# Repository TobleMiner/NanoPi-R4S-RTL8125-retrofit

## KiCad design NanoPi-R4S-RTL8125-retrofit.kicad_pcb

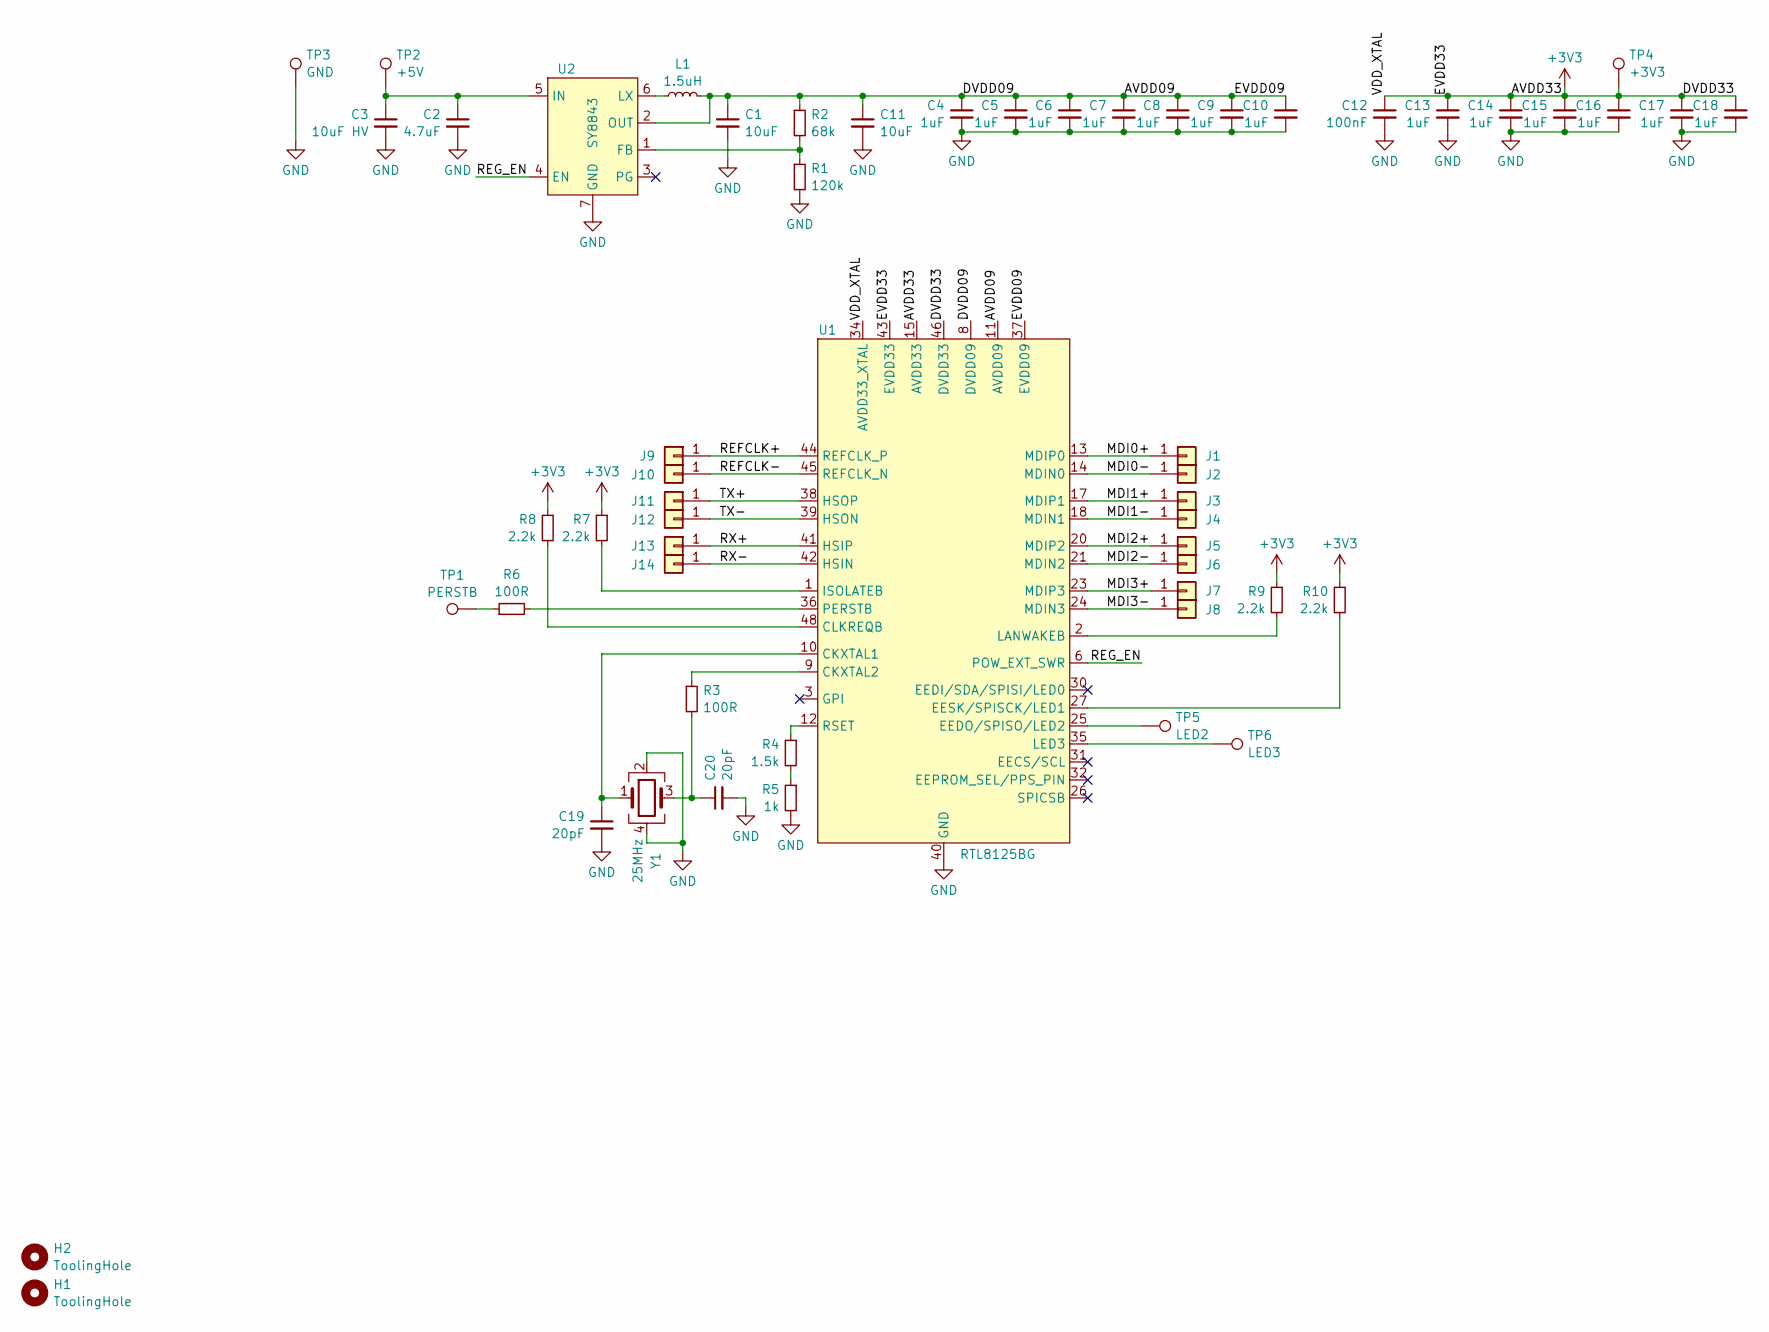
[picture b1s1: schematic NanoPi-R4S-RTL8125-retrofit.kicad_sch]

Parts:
C1, C11: 10uF; C_0402_1005Metric; LCSC C15525
C2: 4.7uF; C_0402_1005Metric; LCSC C23733
C3: 10uF HV; C_0603_1608Metric; LCSC C19702
C4, C5, C6, C7, C8, C9, C10, C13, C14, C15, C16, C17, C18: 1uF; C_0402_1005Metric; LCSC C52923
C12: 100nF; C_0402_1005Metric; LCSC C1525
C19, C20: 20pF; C_0402_1005Metric; LCSC C1554
H1, H2: ToolingHole; ToolingHole_JLCSMT
J1, J2, J3, J4, J5, J6, J7, J8, J9, J10, J11, J12, J13, J14: Conn_01x01; SignalPad
L1: 1.5uH; L_0805_2012Metric; LCSC C334245
R1: 120k; R_0402_1005Metric; LCSC C25750
R2: 68k; R_0402_1005Metric; LCSC C36871
R3, R6: 100R; R_0402_1005Metric; LCSC C25076
R4: 1.5k; R_0402_1005Metric; LCSC C25867
R5: 1k; R_0402_1005Metric; LCSC C11702
R7, R8, R9, R10: 2.2k; R_0402_1005Metric; LCSC C25879
TP1: PERSTB; TestPoint_Pad_D1.0mm
TP2: +5V; TestPoint_Pad_D1.0mm
TP3: GND; TestPoint_Pad_D1.0mm
TP4: +3V3; TestPoint_Pad_D1.0mm
TP5: LED2; TestPoint_Pad_D1.0mm
TP6: LED3; TestPoint_Pad_D1.0mm
U1: RTL8125BG; QFN-48-1EP_6x6mm_P0.4mm_EP4.2x4.2mm_ThermalVias; LCSC C3013605
U2: SY8843; QFN-7_1.5x1.5mm; LCSC C3151906
Y1: 25MHz; Crystal_SMD_2016-4Pin_2.0x1.6mm; LCSC C255883

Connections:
+3V3: C12.1, C13.1, C14.1, C15.1, C16.1, C17.1, C18.1, R7.1, R8.1, R9.1, R10.1, TP4.1, U1.15 (AVDD33), U1.19 (AVDD33), U1.29 (DVDD33), U1.33 (AVDD33), U1.34 (AVDD33_XTAL), U1.43 (EVDD33), U1.46 (DVDD33)
/MDI0+: J1.1, U1.13 (MDIP0)
/MDI0-: J2.1, U1.14 (MDIN0)
/MDI1+: J3.1, U1.17 (MDIP1)
/MDI1-: J4.1, U1.18 (MDIN1)
/MDI2+: J5.1, U1.20 (MDIP2)
/MDI2-: J6.1, U1.21 (MDIN2)
/MDI3+: J7.1, U1.23 (MDIP3)
/MDI3-: J8.1, U1.24 (MDIN3)
/REFCLK+: J9.1, U1.44 (REFCLK_P)
/REFCLK-: J10.1, U1.45 (REFCLK_N)
/REG_EN: U1.6 (POW_EXT_SWR), U2.4 (EN)
/RX+: J13.1, U1.41 (HSIP)
/RX-: J14.1, U1.42 (HSIN)
/TX+: J11.1, U1.38 (HSOP)
/TX-: J12.1, U1.39 (HSON)
AVDD09: C1.1, C4.1, C5.1, C6.1, C7.1, C8.1, C9.1, C10.1, C11.1, L1.2, R2.1, U1.8 (DVDD09), U1.11 (AVDD09), U1.16 (AVDD09), U1.22 (AVDD09), U1.28 (DVDD09), U1.37 (EVDD09), U1.47 (DVDD09), U2.2 (OUT)
GND: C1.2, C2.2, C3.2, C4.2, C5.2, C6.2, C7.2, C8.2, C9.2, C10.2, C11.2, C12.2, C13.2, C14.2, C15.2, C16.2, C17.2, C18.2, C19.2, C20.2, R1.2, R5.2, TP3.1, U1.40 (GND), U1.49 (GND), U2.7 (GND), Y1.2, Y1.4
unnamed: C20.1, R3.2, Y1.3
unnamed: R4.2, R5.1
unnamed: R6.1, TP1.1
unnamed: C19.1, U1.10 (CKXTAL1), Y1.1
unnamed: R3.1, U1.9 (CKXTAL2)
unnamed: R8.2, U1.48 (CLKREQB)
unnamed: TP5.1, U1.25 (EEDO/SPISO/LED2)
unnamed: R10.2, U1.27 (EESK/SPISCK/LED1)
unnamed: R7.2, U1.1 (ISOLATEB)
unnamed: R9.2, U1.2 (LANWAKEB)
unnamed: TP6.1, U1.35 (LED3)
unnamed: R6.2, U1.36 (PERSTB)
unnamed: R4.1, U1.12 (RSET)
unnamed: R1.1, R2.2, U2.1 (FB)
unnamed: C2.1, C3.1, TP2.1, U2.5 (IN)
unnamed: L1.1, U2.6 (LX)

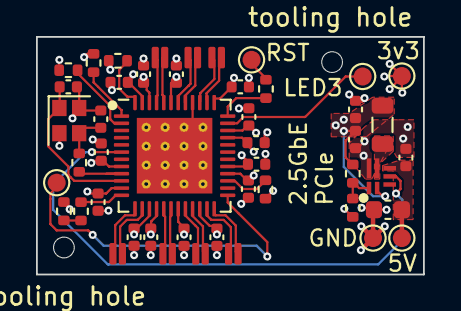
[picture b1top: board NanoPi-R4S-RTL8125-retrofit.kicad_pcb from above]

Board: 4 copper layers, 21.5 x 13.2 mm, 56 parts (0 on the bottom side), 34 nets.

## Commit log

2023-09-23 Finish first layout iteration
2023-09-23 Finalize initial layout revision
2023-09-24 Fix swapped voltage divider on regulator and missing GND on NIC
